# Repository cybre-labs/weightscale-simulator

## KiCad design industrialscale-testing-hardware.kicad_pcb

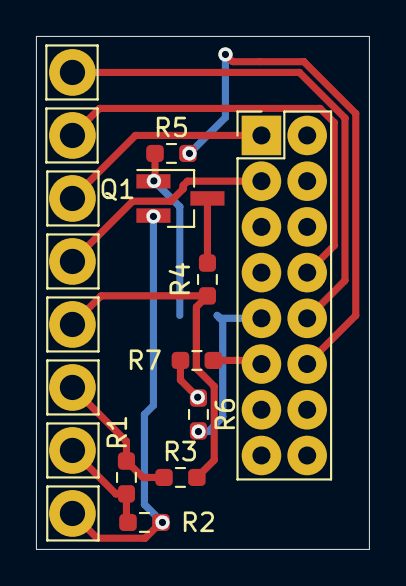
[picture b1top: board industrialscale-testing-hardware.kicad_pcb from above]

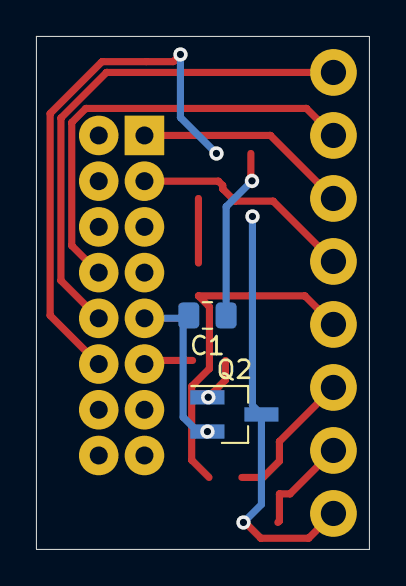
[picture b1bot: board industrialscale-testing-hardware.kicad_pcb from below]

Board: 2 copper layers, 18.5 x 28.5 mm, 19 parts (2 on the bottom side), 14 nets.

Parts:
C1: 10u; C_0805_2012Metric_Pad1.18x1.45mm_HandSolder
J1, J2, J3, J4, J5, J6, J8, J9: Conn_01x01; Pin_D1.4mm_L8.5mm_W2.8mm_FlatFork
J7: Conn_02x08_Odd_Even; PinHeader_2x08_P2.54mm_Vertical_thick
Q1, Q2: AO3400A; SOT-23_Handsoldering
R1, R2, R3, R4: 220R; R_0603_1608Metric_Pad0.98x0.95mm_HandSolder
R5: 7k5; R_0603_1608Metric_Pad0.98x0.95mm_HandSolder
R6: 1M; R_0603_1608Metric_Pad0.98x0.95mm_HandSolder
R7: 100K; R_0603_1608Metric_Pad0.98x0.95mm_HandSolder

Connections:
+3V3: J1.1, R1.1, R3.1
/BOOTMODE: J5.1, J7.3
/RXD: J7.10, J9.1
/TXD: J7.8, J8.1
ANEG: J3.1, R1.2, R2.1
APOS: J2.1, R3.2, R4.1
GND: C1.2, J7.9, Q2.2, R6.2
unnamed: C1.1, Q1.1, R5.1
unnamed: J6.1, J7.1
unnamed: J7.11, R7.1
unnamed: Q1.3, R4.2
unnamed: Q2.1, R6.1, R7.2
RPI_PWM: J7.12, R5.2
SWGND: J4.1, Q1.2, Q2.3, R2.2

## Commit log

2021-04-04 oshpark version
2021-04-04 scad enclosure mod
2021-04-04 modified enclosure once again
2023-05-30 add python script for simulation (WIP)
